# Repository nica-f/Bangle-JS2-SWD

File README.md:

# Bangle-JS2-SWD
KiCad adapter PCB for Bangle.JS2 watch USB-A to 10-pin ST-Link V2

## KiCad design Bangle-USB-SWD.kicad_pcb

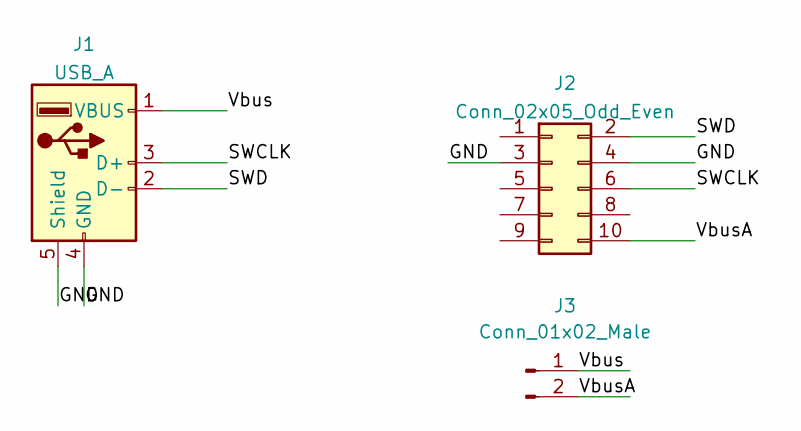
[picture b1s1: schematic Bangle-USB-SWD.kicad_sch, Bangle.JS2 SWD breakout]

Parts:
J1: USB_A; USB_A_Molex_67643_Horizontal
J2: Conn_02x05_Odd_Even; PinHeader_2x05_P2.54mm_Vertical
J3: Conn_01x02_Male; PinHeader_1x02_P2.54mm_Vertical

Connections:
/GND: J1.4 (GND), J1.5 (Shield), J2.3, J2.4
/SWCLK: J1.3 (D+), J2.6
/SWD: J1.2 (D-), J2.2
/Vbus: J1.1 (VBUS), J3.1
/VbusA: J2.10, J3.2

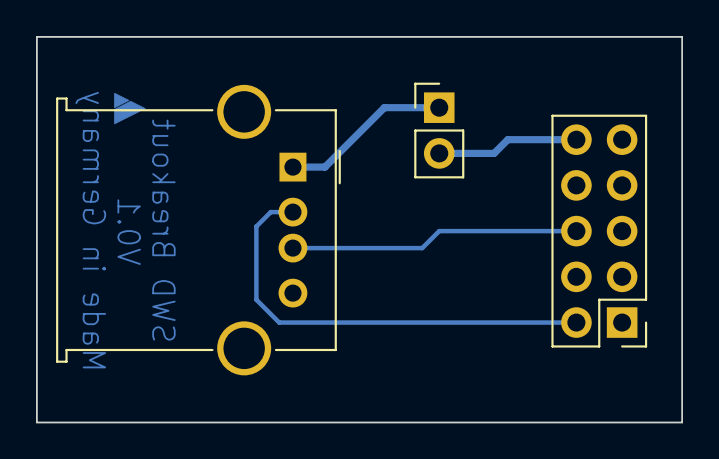
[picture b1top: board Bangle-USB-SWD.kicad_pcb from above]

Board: 2 copper layers, 35.8 x 21.4 mm, 3 parts (0 on the bottom side), 5 nets.

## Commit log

2022-03-20 Add KiCad adapter PCB
2022-03-20 add schematics PDF and top/bottom 3D previews
2022-03-20 oops, SWDIO nd SWCLK swapped on USB type-A conntector, fixed
2022-03-21 fix logo, add 'made in', recreate 3D views

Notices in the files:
Bangle-USB-SWD.kicad_sch:
License: GPL V2.0
